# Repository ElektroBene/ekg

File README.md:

# ekg
ecg/ekg interface between electrodes and oscilloscope

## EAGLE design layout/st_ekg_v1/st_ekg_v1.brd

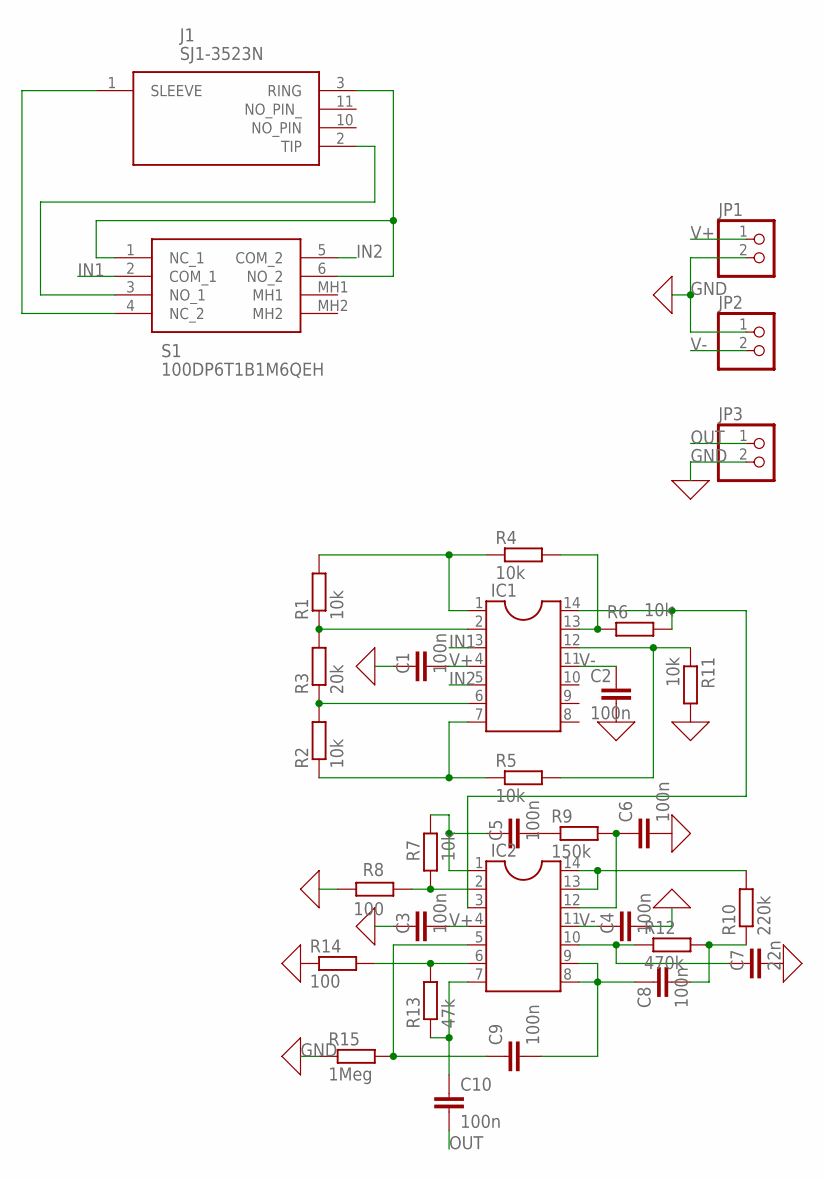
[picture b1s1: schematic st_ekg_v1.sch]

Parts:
C1, C2, C3, C4, C5, C6, C8, C9, C10: 100n; C0805
C7: 22n; C0805
IC1, IC2: DIL14S; SOCKET-14
J1: SJ1-3523N; SJ13523N
JP1, JP2, JP3: PINHD-1X2; 1X02
R1, R2, R4, R5, R6, R7, R11: 10k; M0805
R3: 20k; M0805
R8, R14: 100; M0805
R9: 150k; M0805
R10: 220k; M0805
R12: 470k; M0805
R13: 47k; M0805
R15: 1Meg; M0805
S1: 100DP6T1B1M6QEH

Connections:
GND: C1.1, C2.2, C3.1, C4.2, C6.2, C7.2, JP1.2, JP2.1, JP3.2, R8.2, R11.2, R14.1, R15.1
IN1: IC1.3, S1.2 (COM_1)
IN2: IC1.5, S1.5 (COM_2)
unnamed: J1.2 (TIP), S1.3 (NO_1)
unnamed: J1.3 (RING), S1.1 (NC_1), S1.6 (NO_2)
unnamed: J1.1 (SLEEVE), S1.4 (NC_2)
unnamed: IC1.2, R1.1, R3.2
unnamed: IC1.13, R4.2, R6.1
unnamed: IC1.6, R2.2, R3.1
unnamed: IC1.12, R5.2, R11.1
unnamed: IC1.1, R1.2, R4.1
unnamed: IC1.7, R2.1, R5.1
unnamed: IC1.14, IC2.3, R6.2
unnamed: IC2.2, R7.1, R8.1
unnamed: C5.1, IC2.1, R7.2
unnamed: C5.2, R9.1
unnamed: C6.1, IC2.12, R9.2
unnamed: C8.2, R10.1, R12.2
unnamed: IC2.13, IC2.14, R10.2
unnamed: C7.1, IC2.10, R12.1
unnamed: C8.1, C9.2, IC2.8, IC2.9
unnamed: C9.1, IC2.5, R15.2
unnamed: IC2.6, R13.2, R14.2
unnamed: C10.1, IC2.7, R13.1
OUT: C10.2, JP3.1
V+: C1.2, C3.2, IC1.4, IC2.4, JP1.1
V-: C2.1, C4.1, IC1.11, IC2.11, JP2.2

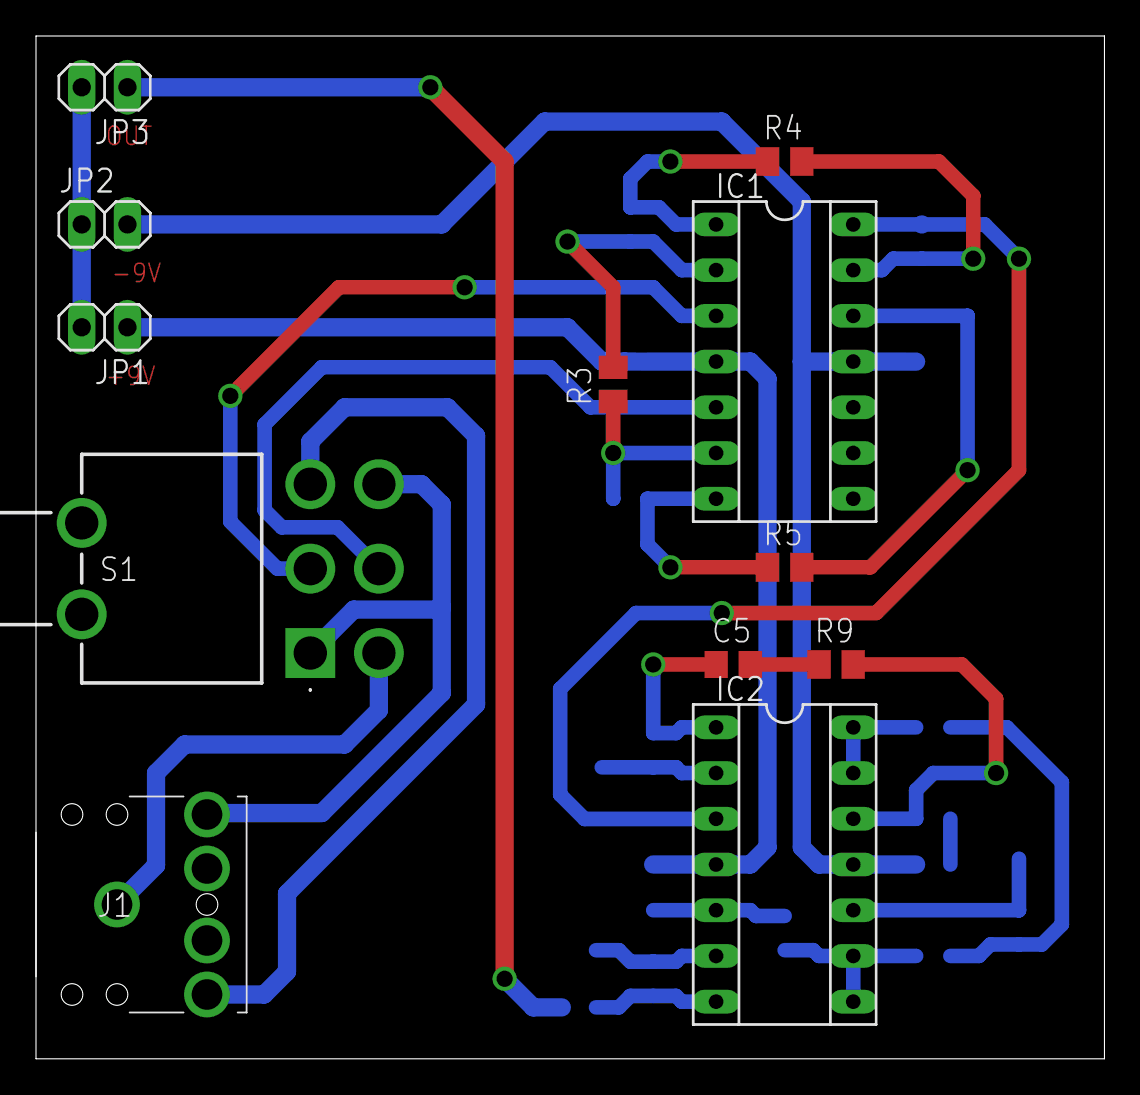
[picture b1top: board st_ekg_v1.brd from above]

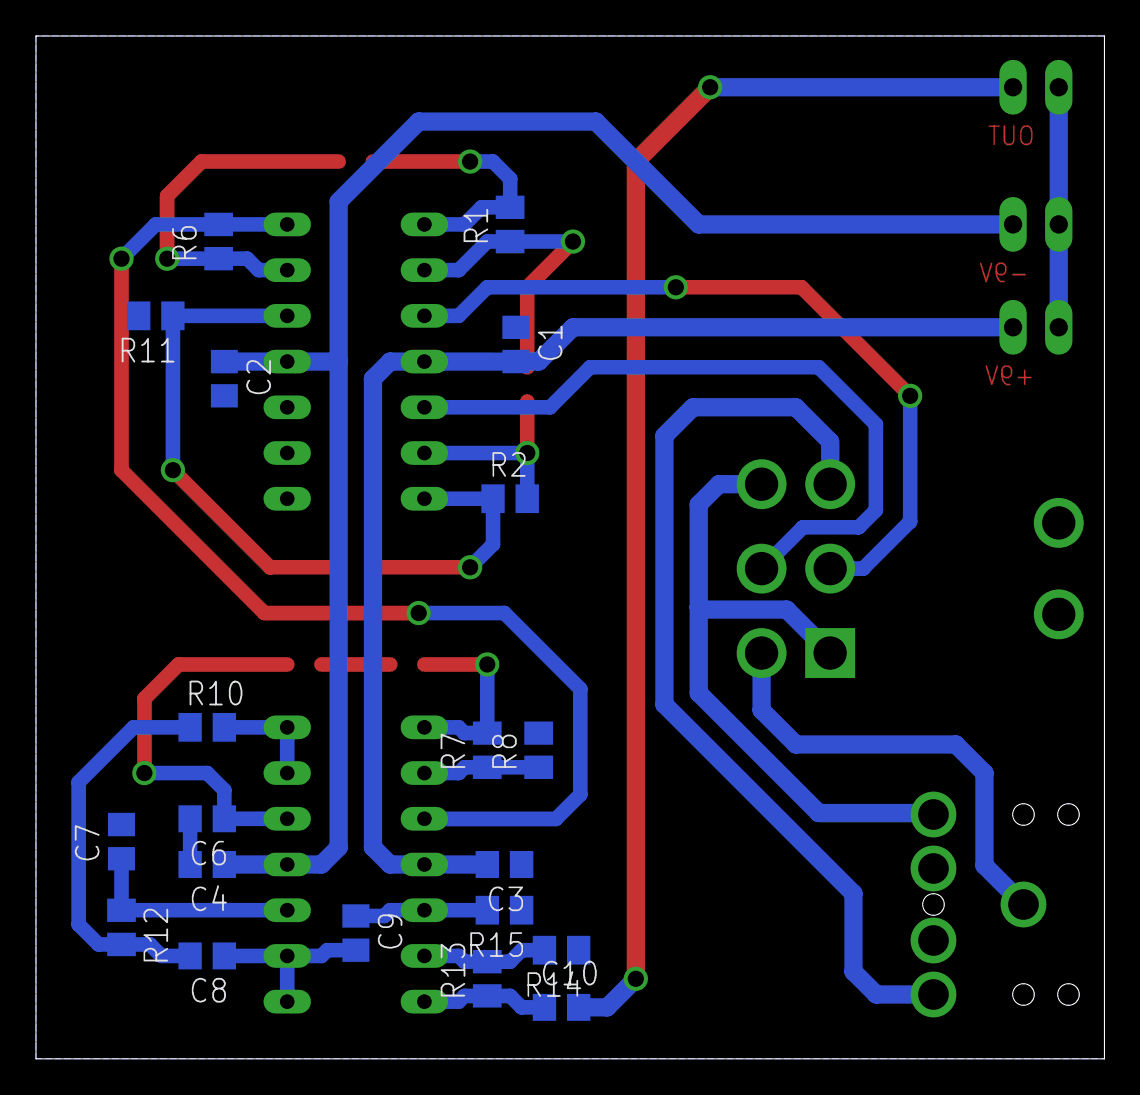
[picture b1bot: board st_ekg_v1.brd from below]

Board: 2 copper layers, 59.4 x 56.8 mm, 32 parts (20 on the bottom side), 27 nets.

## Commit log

2024-12-03 Initial commit including schematics for amplifiers and filters and basic concept
2024-12-15 Add first full version of layout
2024-12-16 Modify layout to include only bottom paths on pin headers
2024-12-17 Minor modifications
2025-01-10 Add first full draft of documentation
2025-01-12 Add photos of layout and schematics
2025-01-12 Add first final draft of documentation
2025-01-12 Add final version of documentation
2025-01-13 Final modifications on final documentation
2025-01-18 Add first draft of final presentation
2025-01-20 Modify final documentation
2025-01-20 Modify final doc again
